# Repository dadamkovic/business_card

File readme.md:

Project in Progress
----------------------------

A PCB for a simple, low profile business card. Intended to be
programmed with a few simple games. BOM cost as of version 0.1 is ~6$.

Includes: 
- 5 LEDs
- buzzer
- STM32F042F6Px (USB communication)

PCB has cutout for components that are inteded to be mounted 'body in'
to decrease the thickness of the PCB (1.2mm PCB used), to get close to
the business card compactness.

Pictures:

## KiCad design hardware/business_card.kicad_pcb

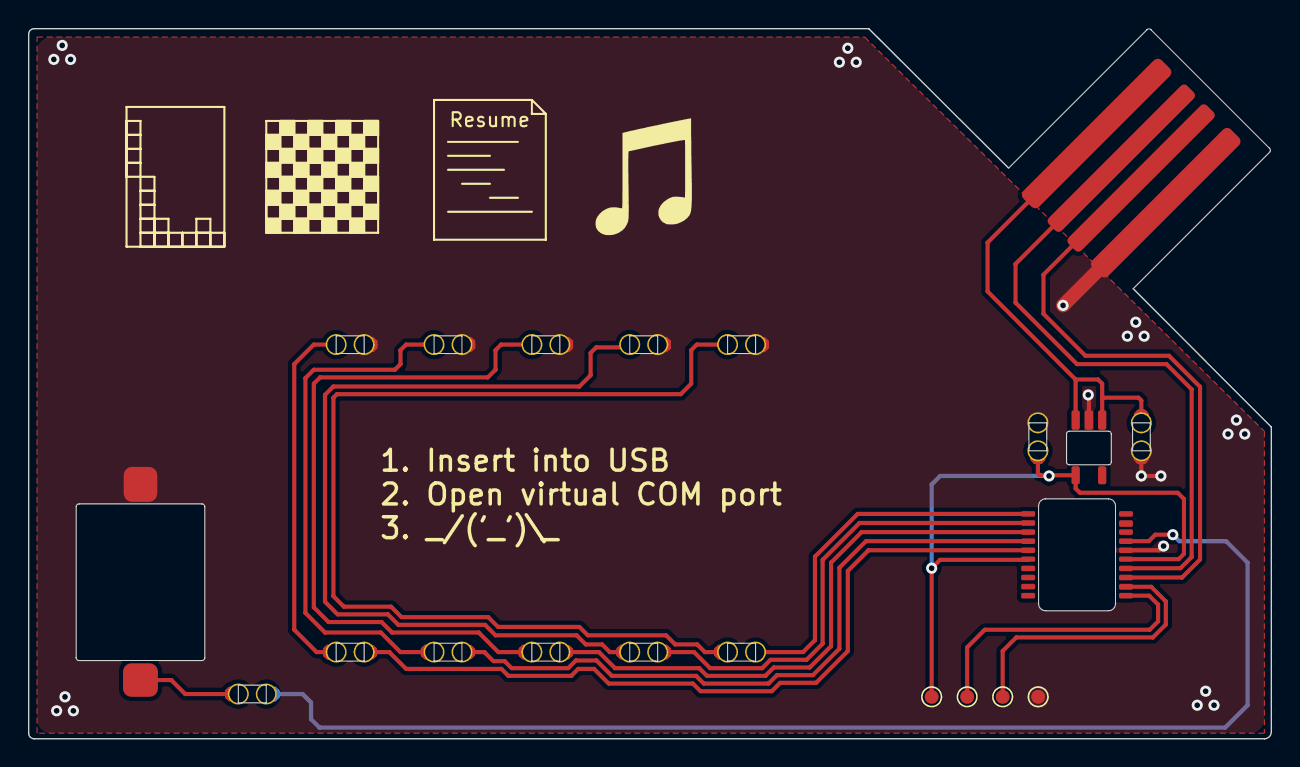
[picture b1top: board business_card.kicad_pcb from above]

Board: 2 copper layers, 88.9 x 50.8 mm, 21 parts (0 on the bottom side), 19 nets.

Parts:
BZ1: Buzzer
C1, C2: C_Small; C_0805_2012Metric
D1, D2, D3, D4, D5: LED; C_0805_2012Metric
J1: Conn_01x04_Pin; USB_Conn
R1, R2, R3, R4, R5, R6: R_Small; C_0805_2012Metric
TP1, TP2, TP3, TP4: TestPoint; TestPoint_Pad_D1.0mm
U1: STM32F042F4Px; Reverse TSSOP-20_4.4x6.5mm_P0.65mm
U2: MIC5504-1.2YM5; SOT-23-5

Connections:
/3V3_SUPPLY: C2.1, TP1.1, U1.5 (VDDA), U1.16 (VDD), U2.5 (VOUT)
/5V_USB: C1.1, J1.1, U2.1 (VIN), U2.3 (EN)
/SWDCLK: TP3.1, U1.20 (PA14)
/SWDIO: TP2.1, U1.19 (PA13)
/USB_DM: J1.2, U1.17 (PA9/PA11)
/USB_DP: J1.3, U1.18 (PA10/PA12)
GND: BZ1.1 (-), C1.2, C2.2, D1.1 (K), D2.1 (K), D3.1 (K), D4.1 (K), D5.1 (K), J1.4, TP4.1, U1.15 (VSSA), U2.2 (GND)
unnamed: BZ1.2 (+), R6.1
unnamed: D1.2 (A), R1.2
unnamed: D2.2 (A), R2.2
unnamed: D3.2 (A), R3.2
unnamed: D4.2 (A), R4.2
unnamed: D5.2 (A), R5.2
unnamed: R5.1, U1.6 (PA0)
unnamed: R4.1, U1.7 (PA1)
unnamed: R3.1, U1.8 (PA2)
unnamed: R1.1, U1.9 (PA3)
unnamed: R2.1, U1.10 (PA4)
unnamed: R6.2, U1.14 (PB1)

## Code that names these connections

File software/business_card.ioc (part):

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Mcu.Name=STM32F042F6Px
Mcu.Package=TSSOP20
Mcu.UserName=STM32F042F6Px
PA0.GPIOParameters=GPIO_Label
PA0.GPIO_Label=LED0
PA0.Signal=GPIO_Output
PA1.GPIOParameters=GPIO_Label
PA1.GPIO_Label=LED1
PA1.Signal=GPIO_Output
PA11.Mode=Device
PA11.Signal=USB_DM
PA12.Mode=Device
PA12.Signal=USB_DP
PA13.Mode=Serial_Wire
PA13.Signal=SYS_SWDIO
PA14.Mode=Serial_Wire
PA14.Signal=SYS_SWCLK
PA2.GPIOParameters=GPIO_Label
PA2.GPIO_Label=LED2
PA2.Signal=GPIO_Output
PA3.GPIOParameters=GPIO_Label
PA3.GPIO_Label=LED3
PA3.Signal=GPIO_Output
PA4.GPIOParameters=GPIO_Label
PA4.GPIO_Label=LED4
PA4.Signal=GPIO_Output
PB1.Signal=S_TIM3_CH4
RCC.SYSCLKFreq_VALUE=48000000
RCC.SYSCLKSource=RCC_SYSCLKSOURCE_HSI48
board=custom

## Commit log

2023-07-03 Routed version v0.1 of the business card.
2023-07-06 Added BOM and readme.
2023-09-30 Commit after restructuring the folder hierarchy
2024-02-18 Re-structured repo files
2025-04-05 Initial version of the menu added.
